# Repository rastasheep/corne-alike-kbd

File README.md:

# Corne alike keyboard
Split keyboard with 3x6 column staggered keys, 3 keys thumb cluster, inspired by [Corne](https://github.com/foostan/crkbd).

## Features

- Designed from the ground up
- Wireless only (no TRRS connectors)
- JST battery connectors
- On/Off switch
- Kailh Choc Switch spacing
- Option to snap off 6th column (3x5 layout as option)
- No OLED module
- No Backlighting

## Repository Contents

- **/pcb** - Pcb design files, made with KiCad, grouped by version (.kicad_pro, .kicad_sch, .kicad_pcb)

## Versions

- **v1.0** - Initial version, Choc v1 switches, full feature set
- **v1.1** - Bug fix version, flip battery connector polarity, fix power input pin

## License Information

Corne alike is open source, released under the [MIT License](/LICENSE.md).

If you have any questions or concerns on licensing, please contact rastasheep@gmail.com.

Distributed as-is; no warranty is given.

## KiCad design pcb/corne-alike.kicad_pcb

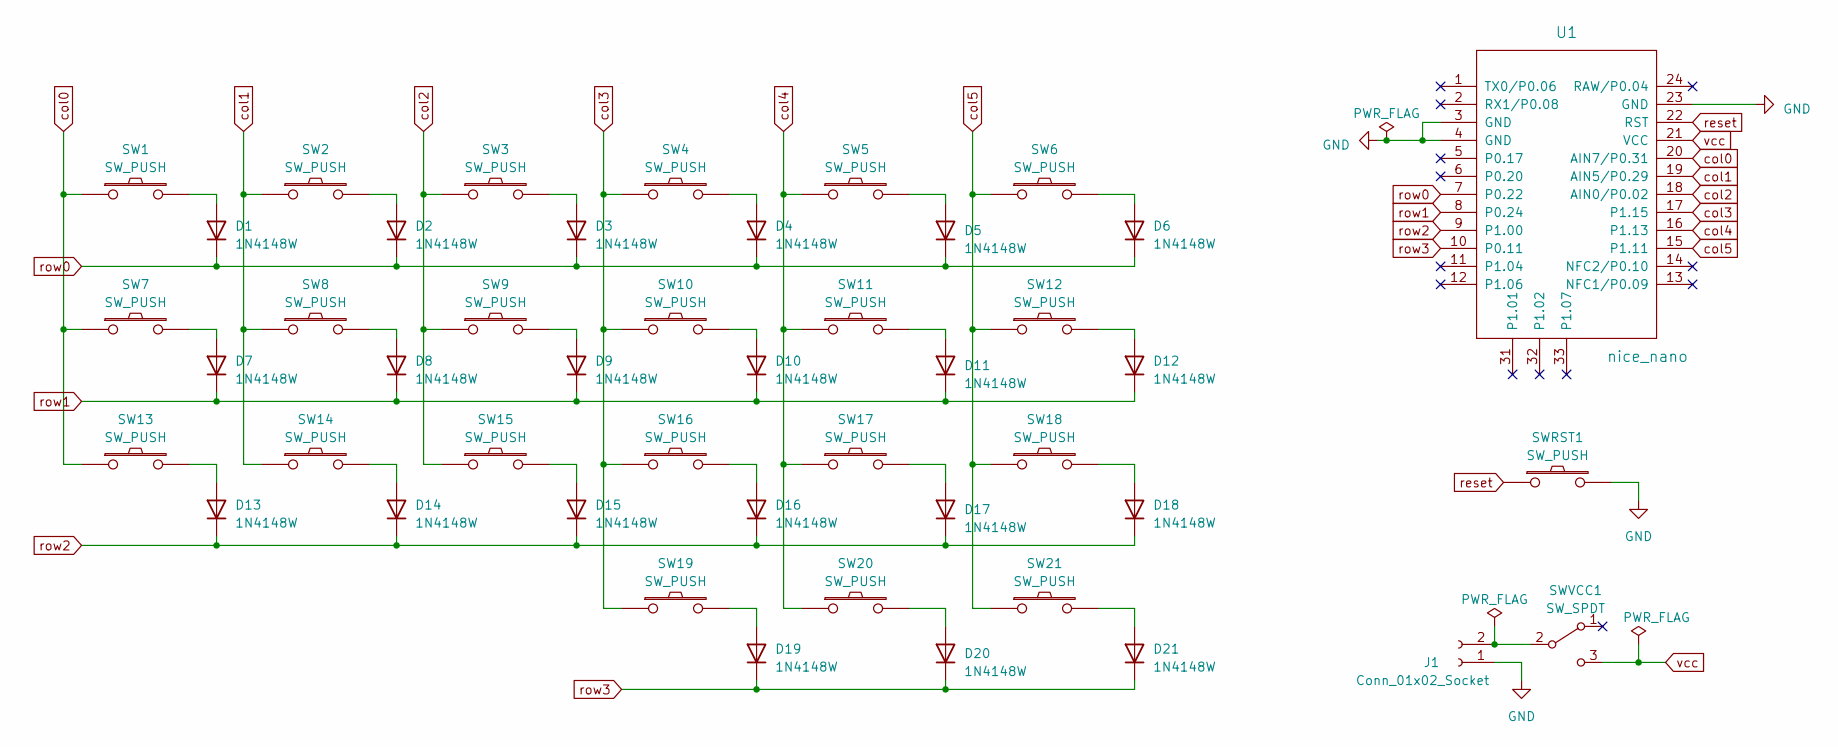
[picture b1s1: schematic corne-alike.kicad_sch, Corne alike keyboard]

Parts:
D1, D2, D3, D4, D5, D6, D7, D8, D9, D10, D11, D12, D13, D14, D15, D16, D17, D18, D19, D20, D21: 1N4148W; D_SOD-123
J1: Conn_01x02_Socket; JST_PH_S2B-PH-SM4-TB_1x02-1MP_P2.00mm_Horizontal
SW1, SW2, SW3, SW4, SW5, SW6, SW7, SW8, SW9, SW10, SW11, SW12, SW13, SW14, SW15, SW16, SW17, SW18, SW19, SW20, SW21: SW_PUSH; Kailh_PG1350
SWRST1: SW_PUSH; SW_TVBP06
SWVCC1: SW_SPDT; SW_EG1218
U1: nice_nano

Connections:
GND: J1.1, SWRST1.2, U1.3 (GND), U1.4 (GND), U1.23 (GND); also elsewhere on the board
unnamed 1: J1.2, SWVCC1.2 (B); also elsewhere on the board
unnamed: D1.2 (A), SW1.2
unnamed: D2.2 (A), SW2.2
unnamed: D3.2 (A), SW3.2
unnamed: D4.2 (A), SW4.2
unnamed: D5.2 (A), SW5.2
unnamed: D6.2 (A), SW6.2
unnamed: D7.2 (A), SW7.2
unnamed: D8.2 (A), SW8.2
unnamed: D9.2 (A), SW9.2
unnamed: D10.2 (A), SW10.2
unnamed: D11.2 (A), SW11.2
unnamed: D12.2 (A), SW12.2
unnamed: D13.2 (A), SW13.2
unnamed: D14.2 (A), SW14.2
unnamed: D15.2 (A), SW15.2
unnamed: D16.2 (A), SW16.2
unnamed: D17.2 (A), SW17.2
unnamed: D18.2 (A), SW18.2
unnamed: D19.2 (A), SW19.2
unnamed: D20.2 (A), SW20.2
unnamed: D21.2 (A), SW21.2
col0: SW1.1, SW7.1, SW13.1, U1.20 (AIN7/P0.31)
col1: SW2.1, SW8.1, SW14.1, U1.19 (AIN5/P0.29)
col2: SW3.1, SW9.1, SW15.1, U1.18 (AIN0/P0.02)
col3: SW4.1, SW10.1, SW16.1, SW19.1, U1.17 (P1.15)
col4: SW5.1, SW11.1, SW17.1, SW20.1, U1.16 (P1.13)
col5: SW6.1, SW12.1, SW18.1, SW21.1, U1.15 (P1.11)
reset: SWRST1.1, U1.22 (RST)
row0: D1.1 (K), D2.1 (K), D3.1 (K), D4.1 (K), D5.1 (K), D6.1 (K), U1.7 (P0.22)
row1: D7.1 (K), D8.1 (K), D9.1 (K), D10.1 (K), D11.1 (K), D12.1 (K), U1.8 (P0.24)
row2: D13.1 (K), D14.1 (K), D15.1 (K), D16.1 (K), D17.1 (K), D18.1 (K), U1.9 (P1.00)
row3: D19.1 (K), D20.1 (K), D21.1 (K), U1.10 (P0.11)
vcc: SWVCC1.3 (C), U1.21 (VCC)

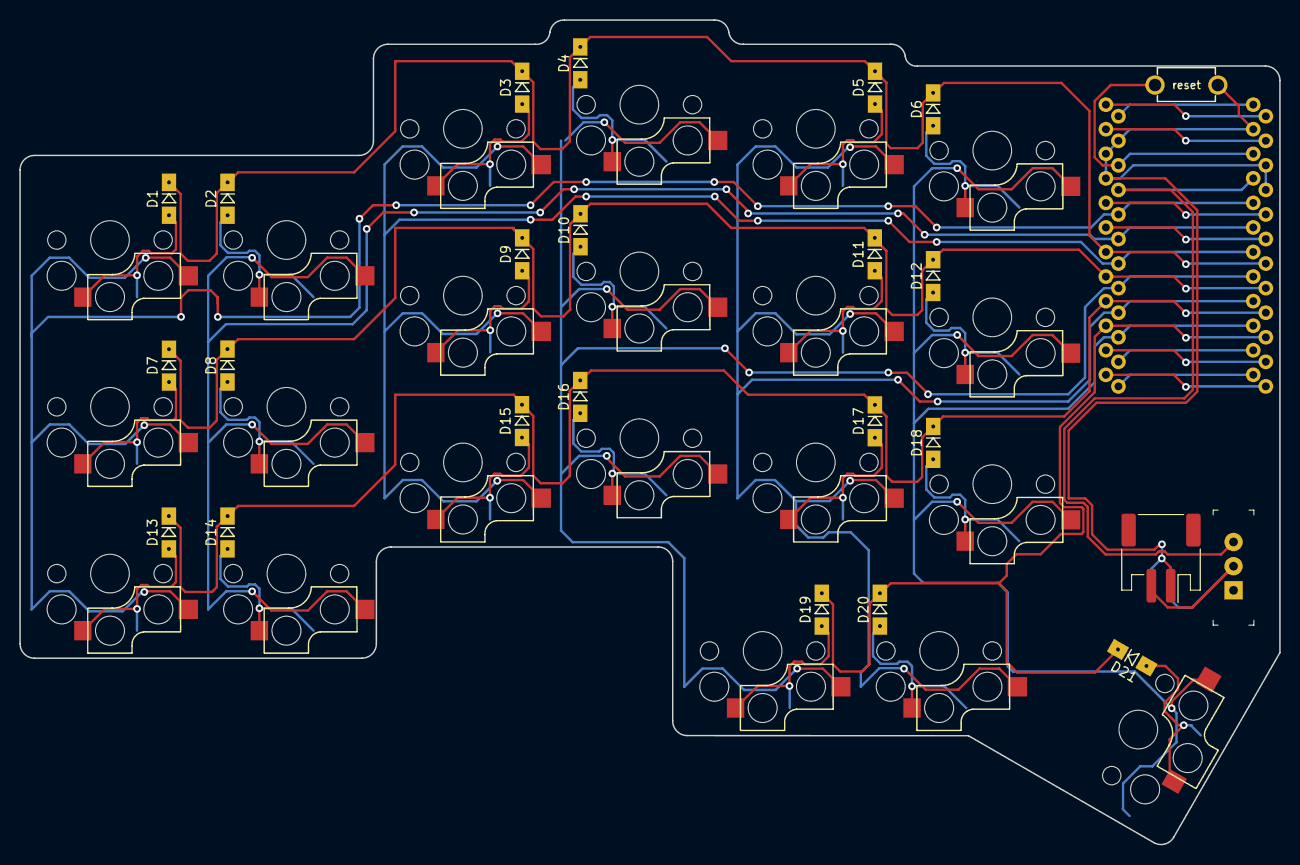
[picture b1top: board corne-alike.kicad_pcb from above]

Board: 2 copper layers, 130.3 x 85.3 mm, 47 parts (1 on the bottom side), 35 nets.

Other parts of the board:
J1#2: Conn_01x02_Socket; JST_PH_S2B-PH-SM4-TB_1x02-1MP_P2.00mm_Horizontal

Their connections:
GND: J1#2.1; also elsewhere on the board
unnamed 1: J1#2.2; also elsewhere on the board

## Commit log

2023-02-16 Generate project, add schema
2023-02-16 Create footprint lib
2023-02-16 Associate footprints and generate pcb
2023-02-17 Place switches and create pcb shape
2023-02-18 Connect switches and diodes
2023-02-19 Connect rows and cols
2023-02-19 Add bat connector, place reset, on/off and bat to pcb
2023-02-20 Clean up tracks, drc violations
2023-02-20 Trace GND, clean up controller escape
2023-02-20 Clean up tracks
2023-02-20 Add hatched copper zone
2023-02-21 Add teardrops, use hatched zone as gnd
2023-02-21 Remove diode labels
2023-02-21 Add board label and version
2023-02-25 Add tabs for breakable cloumn
2023-02-26 Remove unnecessary silkscreen markings
2023-02-26 Organize repo, versions
2023-02-26 Prepare pcb for production
2023-02-26 Generate production file
2023-02-28 Add production gbrs
2023-05-28 Flip battery connector polarity, fix power input pin

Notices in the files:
pcb/corne-alike.kicad_pcb:
License: MIT (https://github.com/rastasheep/corne-alike-kbd/blob/main/LICENSE)
pcb/v1.0/corne-alike.kicad_sch:
License: MIT (https://github.com/rastasheep/corne-alike-kbd/blob/main/LICENSE.md)
